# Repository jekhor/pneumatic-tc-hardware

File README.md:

# Pneumatic tube (bicycle) traffic counter

Inspired by TomorrowLab's early versions of http://www.tomorrow-lab.com/work/waycount

Firmware: https://github.com/jekhor/pneumatic-tc-firmware

# Licensing
License: CC-BY-SA

Copyright 2017-2018 Yauhen Kharuzhy \<jekhor@gmail.com\>

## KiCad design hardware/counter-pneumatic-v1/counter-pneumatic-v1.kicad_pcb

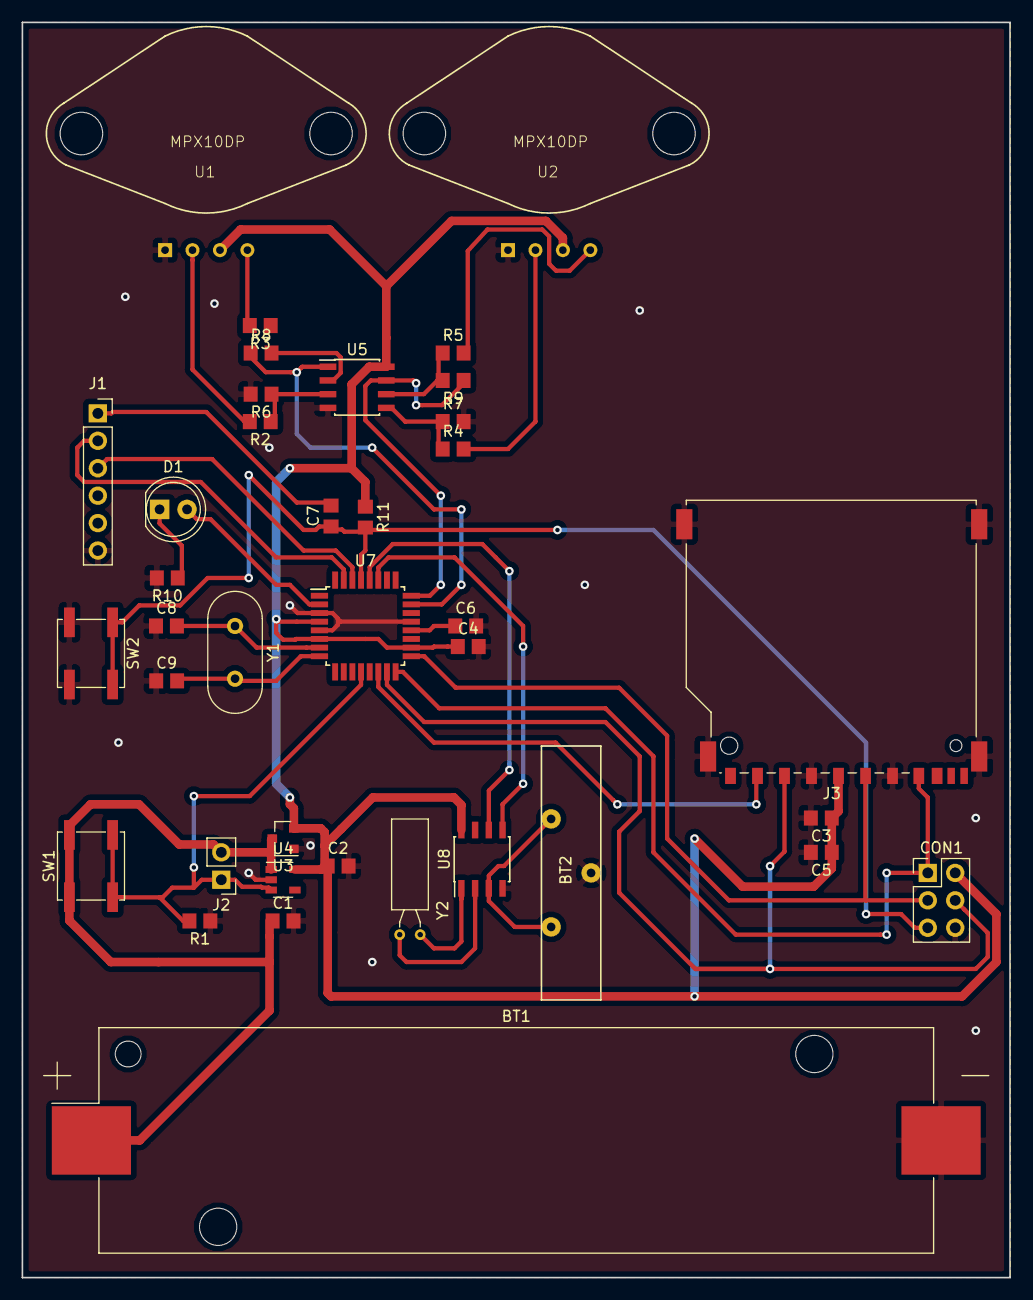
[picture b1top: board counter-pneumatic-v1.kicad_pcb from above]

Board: 2 copper layers, 91.4 x 116.2 mm, 38 parts (0 on the bottom side), 32 nets.

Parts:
BT1: 18650; BatteryHolder_Keystone_1042_1x18650
BT2: CR2032; KLS5-CR2032-04
C1, C2, C3: 1uF; C_0805_2012Metric_Pad1.29x1.40mm_HandSolder
C4, C5, C6, C7: 0,1uF; C_0805_2012Metric_Pad1.29x1.40mm_HandSolder
C8, C9: 22; C_0805_2012Metric_Pad1.29x1.40mm_HandSolder
CON1: AVR-ISP-6; Pin_Header_Straight_2x03_Pitch2.54mm
D1: LED; LED_D5.0mm
J1: Conn_01x06_Female; PinSocket_1x06_P2.54mm_Vertical
J2: Conn_01x02; PinHeader_1x02_P2.54mm_Vertical
J3: SD_Card; SD_TE_2041021
R1, R6, R7, R8, R9: 100K; R_0805_2012Metric_Pad1.29x1.40mm_HandSolder
R2, R3, R4, R5: 2K2; R_0805_2012Metric_Pad1.29x1.40mm_HandSolder
R10: R; R_0805_2012Metric_Pad1.29x1.40mm_HandSolder
R11: 10K; R_0805_2012Metric_Pad1.29x1.40mm_HandSolder
SW1, SW2: SW_Push; SW_SPST_EVPBF
U1, U2: MPX10DP; MPX10DP_Horizontal
U3: MCP1700-3302E_SOT23; SOT-23
U4: NCP551SN33T1G; SOT-23-5
U5: LM358; SOIC-8_3.9x4.9mm_P1.27mm
U7: ATMEGA328-AU; TQFP-32_7x7mm_P0.8mm
U8: DS1338Z-33; SOIC-8_3.9x4.9mm_P1.27mm
Y1: 12 MHz; Crystal_HC49-U_Vertical
Y2: 32768 Hz; Crystal_C38-LF_D3.0mm_L8.0mm_Horizontal

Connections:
+3V3: C2.1, C3.1, C4.1, C5.1, CON1.2, J3.4, R11.1, U1.3, U2.3, U3.2, U4.5, U5.8, U7.4, U7.6, U7.18, U8.8
+BATT: BT1.1, C1.1, J2.2, SW1.1, U3.3, U4.1
/DTR: C7.2, J1.1
/MISO: CON1.1, J3.7, U7.16
/MOSI: CON1.4, J3.2, U7.15
/PRESSURE0: R8.1, U5.1, U7.23
/PRESSURE1: R9.1, U5.7, U7.24
/PWRON: J2.1, R1.2, SW1.2, U4.3, U7.12
/RST: C7.1, CON1.5, R11.2, SW2.1, U7.29
/SCK: CON1.3, J3.5, U7.17
/SCL: U7.28, U8.6
/SDA: U7.27, U8.5
/SD_CS: J3.1, U7.14
GND: BT1.2, BT2.2, C1.2, C2.2, C3.2, C4.2, C5.2, C6.2, C8.1, C9.1, CON1.6, J1.6, J3.3, J3.6, J3.12, R1.1, R6.2, R7.2, R10.2, SW2.2, U1.1, U2.1, U3.1, U4.2, U5.4, U7.3, U7.5, U7.21, U8.4
unnamed: BT2.1, U8.3
unnamed: C6.1, U7.20
unnamed: C8.2, U7.7, Y1.1
unnamed: C9.2, U7.8, Y1.2
unnamed: D1.1, R10.1
unnamed: D1.2, U7.2
unnamed: J1.2, U7.31
unnamed: J1.3, U7.30
unnamed: R2.1, R6.1, U5.3
unnamed: R2.2, U1.2
unnamed: R3.1, R8.2, U5.2
unnamed: R3.2, U1.4
unnamed: R4.1, R7.1, U5.5
unnamed: R4.2, U2.2
unnamed: R5.1, R9.2, U5.6
unnamed: R5.2, U2.4
unnamed: U8.1, Y2.1
unnamed: U8.2, Y2.2

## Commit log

2018-06-16 Add README
2018-06-16 Add STRELKA's manual
2018-07-16 Add datasheets
2018-07-16 Update schematics
2018-07-16 Add PDF schematics
2018-09-08 Update v1 PDF schematics and output files
